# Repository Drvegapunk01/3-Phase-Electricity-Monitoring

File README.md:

# 3-Phase-Electricity-Monitoring

This project is a module to monitor the status of a 3-phase electricity supply and record any power outages. The data can be accessed wirelessly.
Currently, the features are limited to detecting the power state only.

This project was inspired by my father’s question about whether it’s possible to create a device that records power outages at the TV transmitter station where he works.

In the PCB, I use two optocouplers on each phase to capture the full-wave signal. Then, I filter the output with a capacitor to obtain a clean DC signal, which is connected to the ESP32’s I/O pins.

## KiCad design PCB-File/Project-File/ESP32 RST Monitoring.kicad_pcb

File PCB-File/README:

Software yang saya gunakan adalah Kicad 8.0

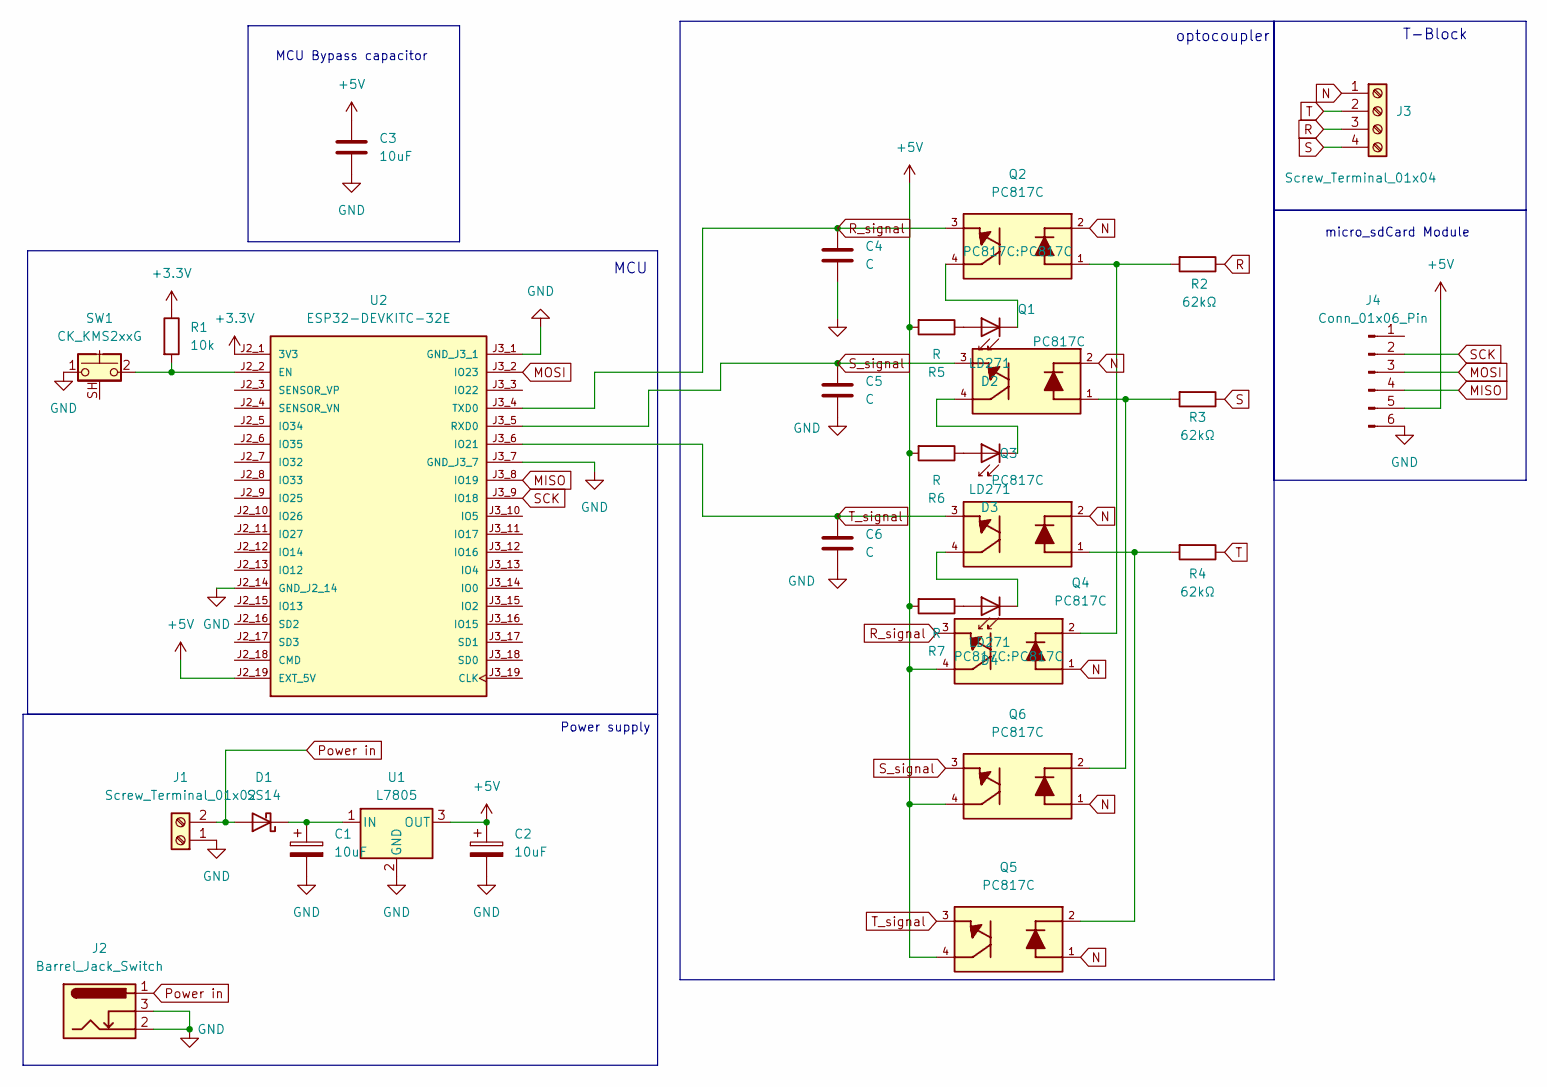
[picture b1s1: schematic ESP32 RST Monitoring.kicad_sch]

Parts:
C1, C2: 10uF; CP_Elec_4x5.4
C3: 10uF; C_0805_2012Metric_Pad1.18x1.45mm_HandSolder
C4, C5, C6: C; C_Elec_4x5.4
D1: SS14; D_SMA
D2, D3, D4: LD271; LED_D5.0mm_IRGrey
J1: Screw_Terminal_01x02; TerminalBlock_bornier-2_P5.08mm
J2: Barrel_Jack_Switch; BarrelJack_Kycon_KLDX-0202-xC_Horizontal
J3: Screw_Terminal_01x04; TerminalBlock_MetzConnect_Type011_RT05504HBWC_1x04_P5.00mm_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
J4: Conn_01x06_Pin; PinSocket_1x06_P2.54mm_Horizontal
Q1, Q2, Q3, Q4, Q5, Q6: PC817C; PARTREV N/A
R1: 10k; R_0805_2012Metric_Pad1.20x1.40mm_HandSolder
R2, R3, R4: 62kΩ; R_Axial_DIN0411_L9.9mm_D3.6mm_P15.24mm_Horizontal
R5, R6, R7: R; R_0805_2012Metric_Pad1.20x1.40mm_HandSolder
SW1: CK_KMS2xxG; SW_SPST_CK_KMS2xxG
U1: L7805; TO-252-3_TabPin2
U2: ESP32-DEVKITC-32E; MODULE_ESP32-DEVKITC-32E; PARTREV 1.4

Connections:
+3.3V: R1.1, U2.J2_1 (3V3)
+5V: C2.1, C3.1, J4.5, Q4.4, Q5.4, Q6.4, R5.2, R6.2, R7.2, U1.3 (OUT), U2.J2_19 (EXT_5V)
GND: C1.2, C2.2, C3.2, C4.2, C5.2, C6.2, J1.1, J2.2, J2.3, J4.6, SW1.1, U1.2 (GND), U2.J2_14 (GND_J2_14), U2.J3_1 (GND_J3_1), U2.J3_7 (GND_J3_7)
MISO: J4.4, U2.J3_8 (IO19)
MOSI: J4.3, U2.J3_2 (IO23)
N: J3.1, Q1.2, Q2.2, Q3.2, Q4.1, Q5.1, Q6.1
unnamed: C1.1, D1.1 (K), U1.1 (IN)
unnamed: D2.2 (A), R5.1
unnamed: D2.1 (K), Q2.4
unnamed: D3.2 (A), R6.1
unnamed: D3.1 (K), Q1.4
unnamed: D4.2 (A), R7.1
unnamed: D4.1 (K), Q3.4
unnamed: Q1.1, Q6.2, R3.2
unnamed: Q2.1, Q4.2, R2.2
unnamed: Q3.1, Q5.2, R4.2
unnamed: R1.2, SW1.2, U2.J2_2 (EN)
Power in: D1.2 (A), J1.2, J2.1
R: J3.3, R2.1
R_signal: C4.1, Q2.3, Q4.3, U2.J3_4 (TXD0)
S: J3.4, R3.1
SCK: J4.2, U2.J3_9 (IO18)
S_signal: C5.1, Q1.3, Q6.3, U2.J3_5 (RXD0)
T: J3.2, R4.1
T_signal: C6.1, Q3.3, Q5.3, U2.J3_6 (IO21)

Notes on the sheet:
micro_sdCard Module
MCU Bypass capacitor
optocoupler
Power supply
T-Block
MCU

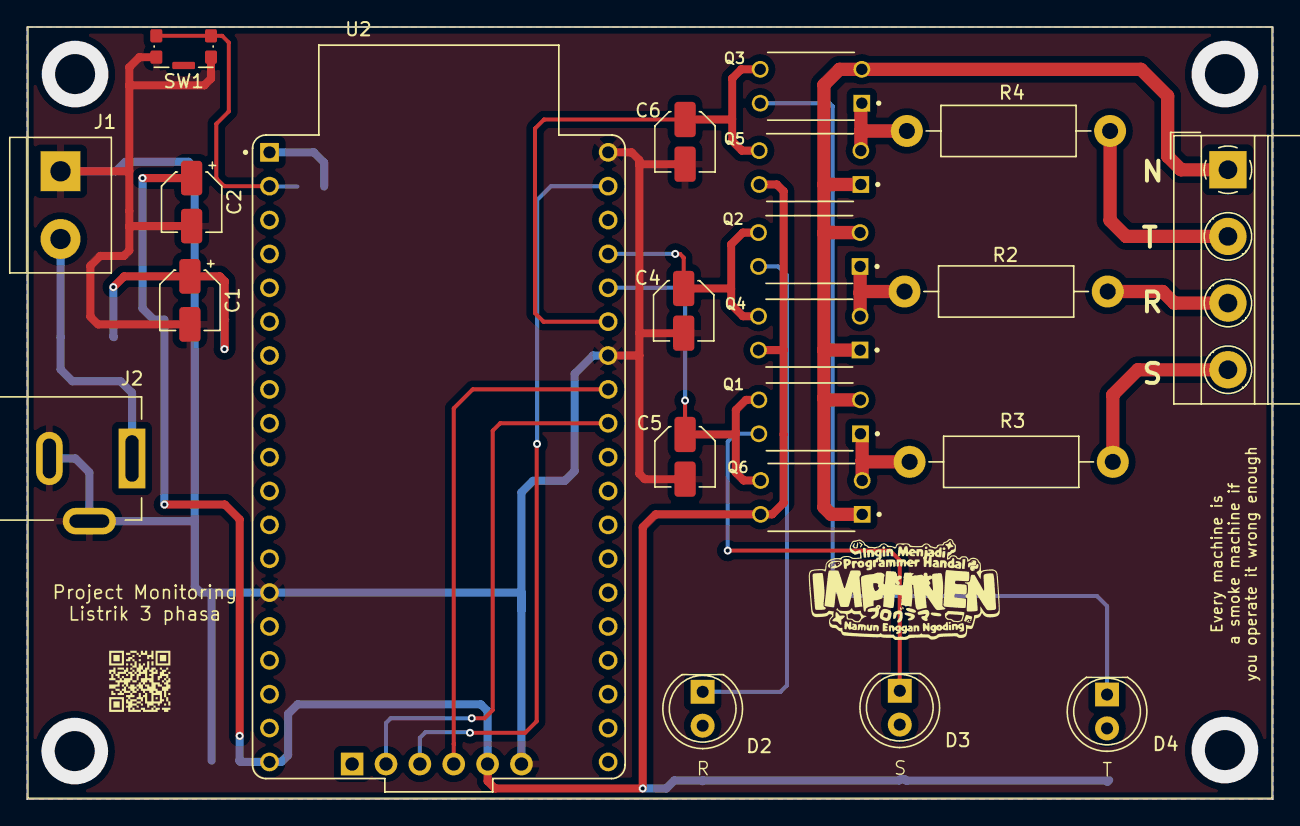
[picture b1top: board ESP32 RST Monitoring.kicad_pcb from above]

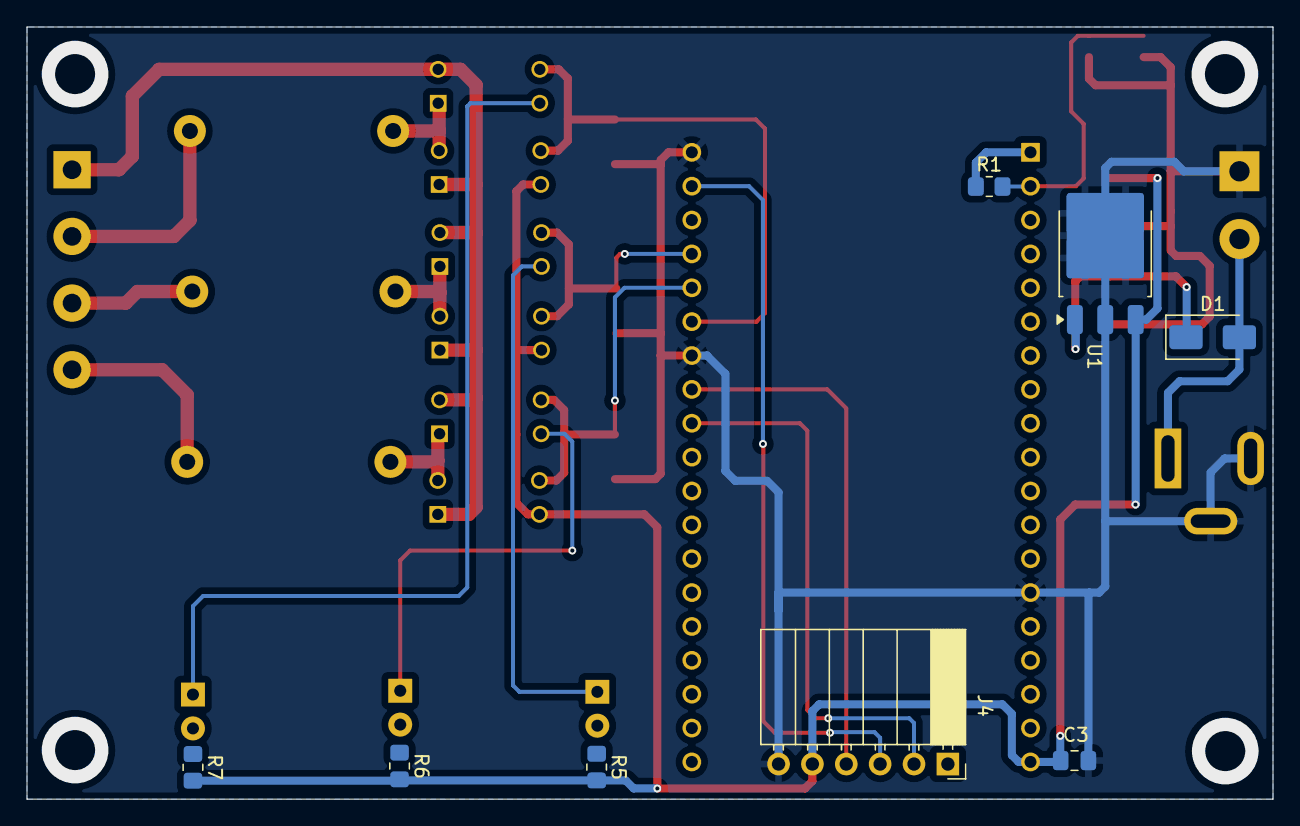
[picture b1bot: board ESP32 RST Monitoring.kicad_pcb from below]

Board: 2 copper layers, 93.4 x 57.9 mm, 30 parts (8 on the bottom side), 25 nets.

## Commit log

2025-06-01 README.md
2025-06-01 README
